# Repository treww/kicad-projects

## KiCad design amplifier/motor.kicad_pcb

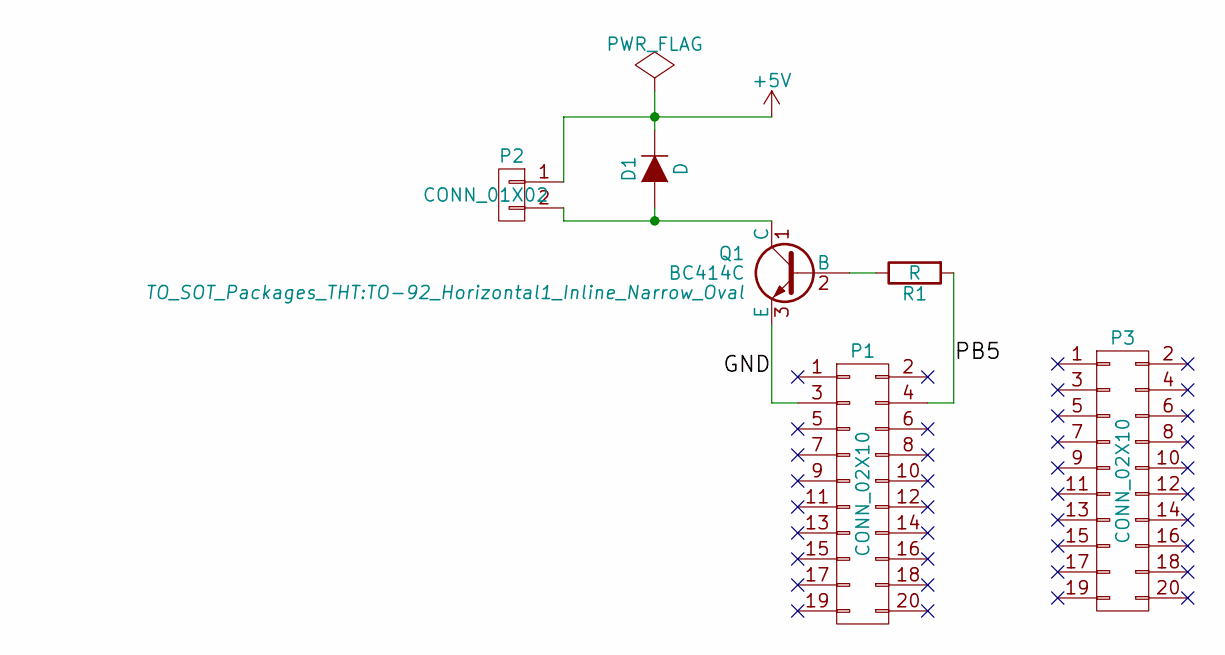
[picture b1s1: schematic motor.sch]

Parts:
D1: D; Diode_DO-35_SOD27_Horizontal_RM10
P1, P3: CONN_02X10; Pin_Header_Straight_2x10
P2: CONN_01X02; Socket_Strip_Angled_1x02
Q1: BC414C; TO-92_Horizontal1_Inline_Narrow_Oval
R1: R; Resistor_Horizontal_RM10mm

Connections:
+5V: D1.1 (K), P2.1
/GND: P1.3, Q1.3 (E)
/PB5: P1.4, R1.2
unnamed: D1.2 (A), P2.2, Q1.1 (C)
unnamed: Q1.2 (B), R1.1

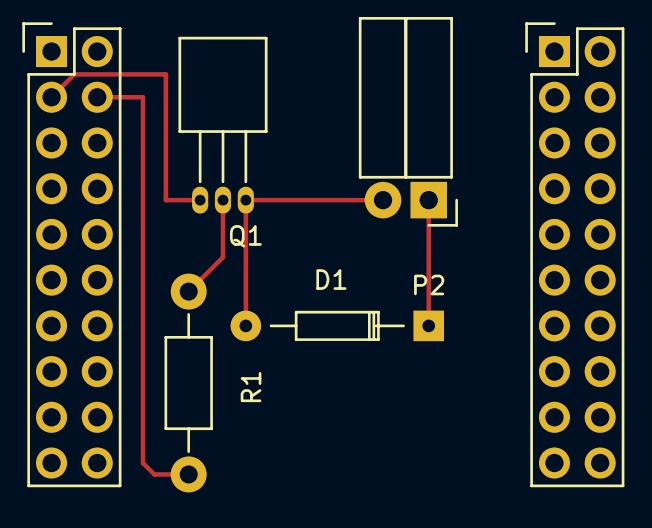
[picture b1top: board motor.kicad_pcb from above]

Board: 2 copper layers, 6 parts (0 on the bottom side), 5 nets.

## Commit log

2015-09-13 first attempt
